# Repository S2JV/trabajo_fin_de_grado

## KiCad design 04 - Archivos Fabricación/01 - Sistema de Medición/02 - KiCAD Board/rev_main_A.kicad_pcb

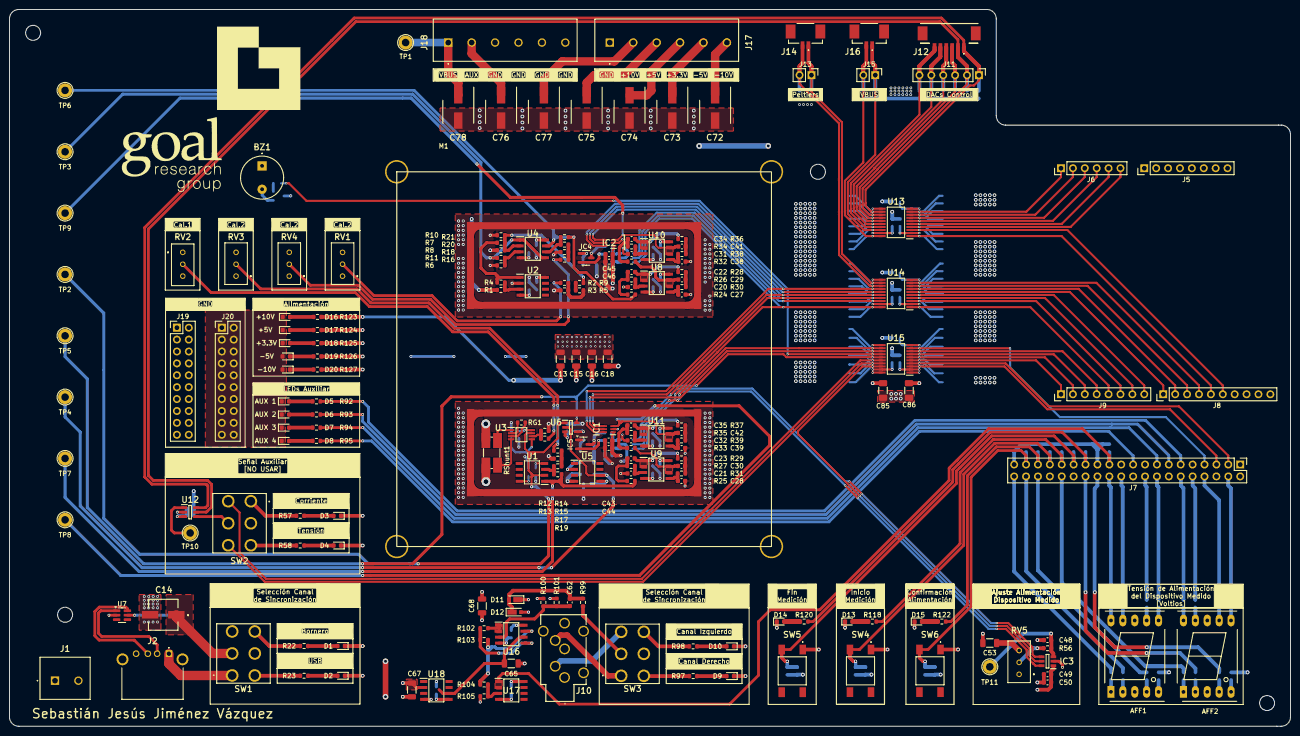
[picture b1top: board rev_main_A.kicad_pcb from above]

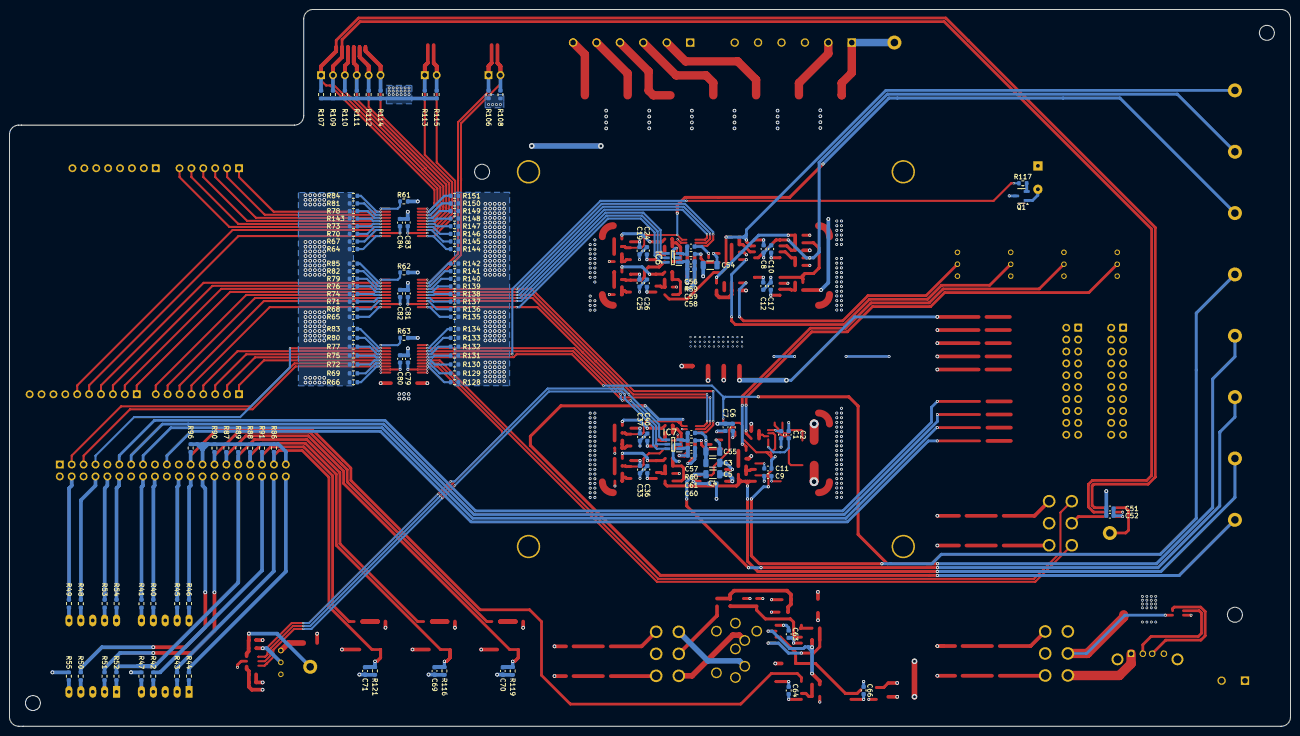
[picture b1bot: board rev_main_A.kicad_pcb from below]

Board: 4 copper layers, 273.5 x 153.0 mm, 334 parts (134 on the bottom side), 197 nets.

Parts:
AFF1, AFF2: TDSR1050; 7SegmentLED_LTS6760_LTS6780
BZ1: CMI-0955-05TH
C1, C2, C6, C7, C8, C9, C10, C11, C12, C17, C19, C24, C25, C26, C33, C36, C37, C40, C43, C45, C49, C51, C56, C57, C58, C60, C63, C64, C79, C80, C81, C82, C83, C84: 0.1u; C_0603_1608Metric
C3, C13, C15, C16, C18, C53, C54, C55, C65, C67, C68: 10u; C_1206_3216Metric
C4, C44, C46, C50, C52, C59, C61, C62, C66, C69, C70, C71: 1u; C_0603_1608Metric
C5: 47u; C_1206_3216Metric
C14: 100u; 865080343009
C20, C21: 100p; C_0603_1608Metric
C22, C23, C29, C30, C34, C35, C41, C42: 1n; C_0603_1608Metric
C27, C28: 430p; C_0603_1608Metric
C31, C32: 680p; C_0603_1608Metric
C38, C39: 910p; C_0603_1608Metric
C48: 15n; C_0603_1608Metric
C72, C73, C74, C75, C76, C77, C78: 47u; CAPAE660X770N
C85, C86: 10u; C_1206_3216Metric_Pad1.33x1.80mm_HandSolder
D1, D2, D3, D4, D5, D6, D7, D8, D9, D10, D13, D15: LED (G); LED_0603_1608Metric
D11, D12: 1V; D_MicroSMP_AK
D14, D16, D17, D18, D19, D20: LED (R); LED_0603_1608Metric
H1, H2, H3, H4: MountingHole; MountingHole_3.2mm_M3
IC1, IC2: AD7476AAKSZ-REEL7; AD7476AAKSZ
IC3, IC6, IC7: ADC121S021CIMFX/NOPB; ADC121S021CIMFXNOPB
IC4, IC5: TMP235A2DBZR; SOT-23-3
J1: Screw_Terminal_01x02; Screw Terminal 2P
J2: USB-1125-GF-B; USB1125GFB [USBA]
J3, J4: MS488-10C
J5: Arduino Power Shield; PinHeader_1x08_P2.54mm_Vertical
J6: Arduino Analog Shield; PinHeader_1x06_P2.54mm_Vertical
J7: Raspberry Pi Shield; PinHeader_2x20_P2.54mm_Vertical
J8: Arduino Digital Shield II; PinHeader_1x10_P2.54mm_Vertical
J9: Arduino Digital Shield I; PinHeader_1x08_P2.54mm_Vertical
J10: SJ1-3533NS; Conector Jack - SJ1-3533NS
J11: Pines; PinHeader_1x06_P2.54mm_Vertical
J12: PicoBlade 6P
J13, J15: PinHeader_1x02_P2.54mm_Vertical
J14, J16: PicoBlade 2P
J17, J18: Screw_Terminal_01x06; Screw Terminal 6P
J19, J20: Conn_02x07_Top_Bottom; PinHeader_2x10_P2.54mm_Vertical
M1: Fan; MC002110
Q1: MMBT4401; SOT-23-3
R1, R4, R6, R7, R8, R11, R19, R40, R41, R42, R43, R44, R45, R46, R47, R48, R49, R50, R51, R52, R53, R54, R55, R116, R117, R119, R121: 1k; R_0603_1608Metric
R2, R13, R14, R16: 200k; R_0603_1608Metric
R3, R12, R15, R18, R59, R60: 100; R_0603_1608Metric
R5, R20: 900; R_0603_1608Metric
R9, R99: 0; R_0603_1608Metric
R10, R103, R105: 100k; R_0603_1608Metric
R17: 1k4; R_0603_1608Metric
R21: 24k; R_0603_1608Metric
R22, R23, R57, R58, R92, R93, R94, R95, R97, R98, R118, R120, R122, R125: 130; R_0603_1608Metric
R24, R25: 1.1k; R_0603_1608Metric
R26, R27: 4.87k; R_0603_1608Metric
R28, R29: 845; R_0603_1608Metric
R30, R31: 1.82k; R_0603_1608Metric
R32, R33: 698; R_0603_1608Metric
R34, R35: 1.58k; R_0603_1608Metric
R36, R37: 715; R_0603_1608Metric
R38, R39: 1.21k; R_0603_1608Metric
R56, R61, R62, R63, R64, R65, R66, R67, R68, R69, R70, R71, R72, R73, R74, R75, R76, R77, R78, R79, R80, R81, R82, R83, R84, R85, R86, R87, R88, R89, R90, R91, R96, R102, R128, R129, R130, R131, R132, R133, R134, R135, R136, R137, R138, R139, R140, R141, R142, R143, R144, R145, R146, R147, R148, R149, R150, R151: 10k; R_0603_1608Metric
R100, R101: 32k; R_0603_1608Metric
R104: 51.5k; R_0603_1608Metric
R106, R107, R108, R109, R110, R111, R112, R113, R114, R115: R; R_0603_1608Metric
R123, R126: 800; R_0603_1608Metric
R124, R127: 300; R_0603_1608Metric
RG1: 60.6; R_0603_1608Metric
RShunt1: 10m; R_Shunt_Ohmite_LVK24
RV1, RV2, RV3, RV4, RV5: 50k; PV36W201C01B00
SW1, SW2, SW3: 100DP1T1B1M2QEH; SW Palanca 100DP1T1B1M2QEH
SW4, SW5, SW6: SW_Push; SW Tactile
TP1, TP2, TP3, TP4, TP5, TP6, TP7, TP8, TP9, TP10, TP11: TestPoint; TestPoint_Loop_D2.60mm_Drill1.6mm_Beaded
U1, U2, U4, U16, U17: OPA210IDBVR; OPA2107AU2K5
U3: INA849DGKT
U5: REF5030AIDR
U6: TLV3601QDBVRQ1
U7: IP4234CZ6,125; SC-74-6_1.55x2.9mm_P0.95mm
U8, U9, U10, U11: AD8656ARZ
U12: DAC121S101CIMK_NOPB
U13, U14, U15: TXS0108EPWRG4
U18: REF5025AIDR; REF5030AIDR

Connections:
+3.3V: C74.1, C80.1, C82.1, C84.1, C86.1, J5.5, J5.7, J7.1, J7.17, J17.4, R47.1, R61.1, R62.1, R63.1, R125.2, SW1.5 (B), SW2.2 (B), SW3.5 (B), SW4.1, SW5.1, SW6.1, U13.2 (VCCA), U14.2 (VCCA), U15.2 (VCCA)
+5V: BZ1.1 (+), C3.1, C6.1, C16.1, C19.1, C25.1, C33.1, C37.1, C43.2, C44.2, C45.2, C46.2, C49.2, C50.2, C51.2, C52.2, C53.1, C54.1, C55.1, C58.2, C59.2, C60.2, C61.2, C63.1, C64.1, C67.1, C68.1, C75.1, C79.1, C81.1, C83.1, C85.1, IC1.1 (VDD), IC2.1 (VDD), IC3.1 (VDD), IC4.1 (VDD), IC5.1 (VDD), IC6.1 (VDD), IC7.1 (VDD), J5.4, J7.2, J17.3, R100.1, R124.2, RV1.1, RV2.3, RV3.1, RV4.1, RV5.3, U5.2 (Vin), U6.3 (V+), U8.8 (V+), U9.8 (V+), U10.8 (V+), U11.8 (V+), U12.3 (VA), U13.19 (VCCB), U14.19 (VCCB), U15.19 (VCCB), U16.8 (V+), U17.8 (V+), U18.2 (Vin)
+10V: C1.2, C8.1, C9.1, C12.1, C13.1, C77.1, J17.2, R123.2, U1.8 (V+), U2.8 (V+), U3.8 (Vs+), U4.8 (V+)
-5V: C7.1, C18.1, C24.1, C26.1, C36.1, C40.1, C73.1, J17.5, R127.2, RV1.3, RV2.1, RV3.3, RV4.3, U6.4 (V-), U8.4 (V-), U9.4 (V-), U10.4 (V-), U11.4 (V-)
-10V: C2.2, C10.1, C11.1, C15.1, C17.1, C72.1, J17.6, R126.2, U1.4 (V-), U2.4 (V-), U3.5 (Vs-), U4.4 (V-)
/006_Conn_FPGA1/BUZZER_{FPGA}: J9.3, R77.1, U15.7 (A6)
/006_Conn_FPGA1/CD_{BUS,ADC,FPGA}: J9.5, R65.1, U14.1 (A1)
/006_Conn_FPGA1/CLK_{4MHz,FPGA}: J9.7, R71.1, U14.4 (A3)
/006_Conn_FPGA1/CLK_{ADC,FPGA}: J9.8, R74.1, U14.5 (A4)
/006_Conn_FPGA1/CLK_{DAC,FPGA}: J6.2, R81.1, U13.8 (A7)
/006_Conn_FPGA1/CS_{ADC,FPGA}: J8.2, R79.1, U14.7 (A6)
/006_Conn_FPGA1/DATA_{BUS,ADC,FPGA}: J7.5, R66.1, U15.3 (A2)
/006_Conn_FPGA1/DATA_{I,ADC,FPGA}: J9.4, R80.1, U15.8 (A7)
/006_Conn_FPGA1/DATA_{TEMP,I,FPGA}: J7.7, R83.1, U15.9 (A8)
/006_Conn_FPGA1/DATA_{TEMP,V,FPGA}: J9.6, R68.1, U14.3 (A2)
/006_Conn_FPGA1/DATA_{V,ADC,FPGA}: J8.1, R76.1, U14.6 (A5)
/006_Conn_FPGA1/DIN_{DAC,AUX,FPGA}: J6.6, R70.1, U13.4 (A3)
/006_Conn_FPGA1/DIN_{DAC,BUS,FPGA}: J6.5, R73.1, U13.5 (A4)
/006_Conn_FPGA1/DIN_{DAC,PEL,I,FPGA}: J6.3, R78.1, U13.7 (A6)
/006_Conn_FPGA1/DIN_{DAC,PEL,V,FPGA}: J6.4, R143.1, U13.6 (A5)
/006_Conn_FPGA1/DIN_{I,AUX,FPGA}: J7.3, R69.1, U15.4 (A3)
/006_Conn_FPGA1/DIN_{V,AUX,FPGA}: J9.1, R72.1, U15.5 (A4)
/006_Conn_FPGA1/ENABLE_{BUS,AUX,FPGA}: J8.6, R67.1, U13.3 (A2)
/006_Conn_FPGA1/ENABLE_{BUS,FPGA}: J8.5, R64.1, U13.1 (A1)
/006_Conn_FPGA1/ENABLE_{PEL,I,FPGA}: J8.4, R85.1, U14.9 (A8)
/006_Conn_FPGA1/ENABLE_{PEL,V,FPGA}: J8.3, R82.1, U14.8 (A7)
/006_Conn_FPGA1/LED_{AUX,1}: J7.11, R92.2
/006_Conn_FPGA1/LED_{AUX,2}: J7.13, R93.2
/006_Conn_FPGA1/LED_{AUX,3}: J7.15, R94.2
/006_Conn_FPGA1/LED_{AUX,4}: J7.19, R95.2
/006_Conn_FPGA1/Protection_{Trigger,FPGA}: J9.2, R75.1, U15.6 (A5)
/006_Conn_FPGA1/SYNC_{DAC,FPGA}: J6.1, R84.1, U13.9 (A8)
ADC_{I,In}: C42.2, IC1.3 (VIN), TP8.1, U11.6 (-), U11.7
ADC_{V,In}: C41.2, IC2.3 (VIN), TP9.1, U10.6 (-), U10.7
BUZZER: R117.2, R132.1, U15.14 (B6)
CLK_{4MHz}: IC3.4 (SCLK), IC6.4 (SCLK), IC7.4 (SCLK), R137.1, U14.17 (B3)
CLK_{ADC}: IC1.4 (SCLK), IC2.4 (SCLK), R138.1, U14.16 (B4)
CLK_{DAC}: J11.2, J12.2, R109.1, R150.1, U12.5 (SCLK), U13.13 (B7)
CS_{ADC}: IC1.6 (~CS), IC2.6 (~CS), R140.1, U14.14 (B6)
CS_{BUS,ADC}: IC3.6 (~CS), IC6.6 (~CS), IC7.6 (~CS), R135.1, U14.20 (B1)
DATA_{BUS,ADC}: IC3.5 (SDATA), R128.1, U15.18 (B2)
DATA_{I,ADC}: IC1.5 (SDATA), R133.1, U15.13 (B7)
DATA_{TEMP,I}: IC7.5 (SDATA), R134.1, U15.12 (B8)
DATA_{TEMP,V}: IC6.5 (SDATA), R136.1, U14.18 (B2)
DATA_{V,ADC}: IC2.5 (SDATA), R139.1, U14.15 (B5)
DIN_{DAC,AUX}: J11.6, J12.6, R114.1, R146.1, U13.17 (B3)
DIN_{DAC,BUS}: J11.5, J12.5, R112.1, R147.1, U13.16 (B4)
DIN_{DAC,PEL,I}: J11.3, J12.3, R110.1, R149.1, U13.14 (B6)
DIN_{DAC,PEL,V}: J11.4, J12.4, R111.1, R148.1, U13.15 (B5)
DIN_{I,AUX}: R129.1, SW2.6 (C), U15.17 (B3)
DIN_{V,AUX}: R130.1, SW2.4 (A), U15.16 (B4)
Display1_{a}: J7.18, R40.1
Display1_{b}: J7.16, R41.1
Display1_{c}: J7.36, R42.1
Display1_{d}: J7.38, R43.1
Display1_{e}: J7.40, R44.1
Display1_{f}: J7.22, R45.1
Display1_{g}: J7.24, R46.1
Display2_{a}: J7.8, R48.1
Display2_{b}: J7.4, R49.1
Display2_{c}: J7.26, R50.1
Display2_{d}: J7.28, R51.1
Display2_{e}: J7.32, R52.1
Display2_{f}: J7.10, R53.1
Display2_{g}: J7.12, R54.1
ENABLE_{BUS,AUX}: J15.1, J16.1, R113.1, R145.1, U13.18 (B2)
ENABLE_{BUS}: J15.2, J16.2, R115.1, R144.1, U13.20 (B1)
ENABLE_{PEL,I}: J13.1, J14.1, R106.1, R142.1, U14.12 (B8)
ENABLE_{PEL,V}: J13.2, J14.2, R108.1, R141.1, U14.13 (B7)
GND: AFF1.3 (C.A.), AFF1.8 (C.A.), AFF2.3 (C.A.), AFF2.8 (C.A.), C1.1, C2.1, C3.2, C4.2, C5.2, C6.2, C7.2, C8.2, C9.2, C10.2, C11.2, C12.2, C13.2, C14.2, C15.2, C16.2, C17.2, C18.2, C19.2, C20.2, C21.2, C24.2, C25.2, C26.2, C27.2, C28.2, C31.2, C32.2, C33.2, C36.2, C37.2, C38.2, C39.2, C40.2, C43.1, C44.1, C45.1, C46.1, C48.2, C49.1, C50.1, C51.1, C52.1, C53.2, C54.2, C55.2, C56.2, C57.2, C58.1, C59.1, C60.1, C61.1, C63.2, C64.2, C65.2, C66.2, C67.2, C68.2, C69.2, C70.2, C71.2, C72.2, C73.2, C74.2, C75.2, C76.2, C77.2, C78.2, C79.2, C80.2, C81.2, C82.2, C83.2, C84.2, C85.2, C86.2, D1.1 (K), D2.1 (K), D3.1 (K), D4.1 (K), D5.1 (K), D6.1 (K), D7.1 (K), D8.1 (K), D9.1 (K), D10.1 (K), D11.1 (K), D12.2 (A), D13.1 (K), D14.1 (K), D15.1 (K), D16.1 (K), D17.1 (K), D18.1 (K), D19.2 (A), D20.2 (A), IC1.2 (GND), IC2.2 (GND), IC3.2 (GND), IC4.3 (GND), IC5.3 (GND), IC6.2 (GND), IC7.2 (GND), J1.1, J2.4 (GND), J2.5 (Shield), J3.1 (Shield), J4.1 (Shield), J5.2, J5.3, J7.6, J7.9, J7.14, J7.20, J7.25, J7.30, J7.34, J7.39, J8.7, J10.1, J17.1, J18.3, J18.4, J18.5, J18.6, J19.1, J19.2, J19.3, J19.4, J19.5, J19.6, J19.7, J19.8, J19.9, J19.10, J19.11, J19.12, J19.13, J19.14, J19.15, J19.16, J19.17, J19.18, J19.19, J19.20, J20.1, J20.2, J20.3, J20.4, J20.5, J20.6, J20.7, J20.8, J20.9, J20.10, J20.11, J20.12, J20.13, J20.14, J20.15, J20.16, J20.17, J20.18, J20.19, J20.20, M1.1 (+), Q1.3 (E), R3.1, R6.1, R10.1, R12.1, R15.2, R18.2, R55.1, R64.2, R65.2, R66.2, R67.2, R68.2, R69.2, R70.2, R71.2, R72.2, R73.2, R74.2, R75.2, R76.2, R77.2, R78.2, R79.2, R80.2, R81.2, R82.2, R83.2, R84.2, R85.2, R86.2, R87.2, R88.2, R89.2, R90.2, R91.2, R96.2, R101.2, R105.2, R106.2, R107.2, R108.2, R109.2, R110.2, R111.2, R112.2, R113.2, R114.2, R115.2, R116.2, R119.2, R121.2, R128.2, R129.2, R130.2, R131.2, R132.2, R133.2, R134.2, R135.2, R136.2, R137.2, R138.2, R139.2, R140.2, R141.2, R142.2, R143.2, R144.2, R145.2, R146.2, R147.2, R148.2, R149.2, R150.2, R151.2, RV5.1, U2.2 (-), U5.4 (GND), U7.2 (VN), U12.2 (GND), U13.11 (GND), U14.11 (GND), U15.11 (GND), U16.4 (V-), U17.4 (V-), U18.4 (GND)
I_{Measure}: R19.2, R25.1, TP7.1, U1.1
unnamed: AFF1.5 (DP), R47.2
unnamed: AFF1.7 (a), R40.2
unnamed: AFF1.6 (b), R41.2
unnamed: AFF1.4 (c), R42.2
unnamed: AFF1.2 (d), R43.2
unnamed: AFF1.1 (e), R44.2
unnamed: AFF1.9 (f), R45.2
unnamed: AFF1.10 (g), R46.2
unnamed: AFF2.5 (DP), R55.2
unnamed: AFF2.7 (a), R48.2
unnamed: AFF2.6 (b), R49.2
unnamed: AFF2.4 (c), R50.2
unnamed: AFF2.2 (d), R51.2
unnamed: AFF2.1 (e), R52.2
unnamed: AFF2.9 (f), R53.2
unnamed: AFF2.10 (g), R54.2
unnamed: BZ1.2 (-), Q1.1 (C)
unnamed: C22.1, R24.2, R26.1
unnamed: C23.1, R25.2, R27.1
unnamed: C29.1, R28.2, R30.1
unnamed: C30.1, R29.2, R31.1
unnamed: C34.1, R32.2, R34.1
unnamed: C35.1, R33.2, R35.1
unnamed: C41.1, R36.2, R38.1
unnamed: C42.1, R37.2, R39.1
unnamed: D1.2 (A), R22.1
unnamed: D2.2 (A), R23.1
unnamed: D3.2 (A), R57.1
unnamed: D4.2 (A), R58.1
unnamed: D5.2 (A), R92.1
unnamed: D6.2 (A), R93.1
unnamed: D7.2 (A), R94.1
unnamed: D8.2 (A), R95.1
unnamed: D9.2 (A), R97.1
unnamed: D10.2 (A), R98.1
unnamed: C62.1, D11.2 (A), D12.1 (K), R99.2
unnamed: D13.2 (A), R118.1
unnamed: D14.2 (A), R120.1
unnamed: D15.2 (A), R122.1
unnamed: D16.2 (A), R123.1
unnamed: D17.2 (A), R124.1
unnamed: D18.2 (A), R125.1
unnamed: D19.1 (K), R126.1
unnamed: D20.1 (K), R127.1
unnamed: C48.1, IC3.3 (VIN), R56.2, TP11.1
unnamed: IC4.2 (VOUT), R59.1
unnamed: IC5.2 (VOUT), R60.1
unnamed: C56.1, IC6.3 (VIN), R59.2
unnamed: C57.1, IC7.3 (VIN), R60.2
unnamed: J1.2, SW1.3 (C)
unnamed: J2.3 (D+), U7.6
unnamed: J2.2 (D-), U7.1
unnamed: J2.1 (VBUS), SW1.1 (A)
unnamed: J10.2, SW3.3 (C)
unnamed: J10.3, SW3.1 (A)
unnamed: Q1.2 (B), R117.1
unnamed: R2.1, RV1.2
unnamed: R2.2, R3.2, R5.1
unnamed: R4.2, R7.1, U2.1
unnamed: R5.2, R9.1
unnamed: R13.2, RV2.2
unnamed: R14.1, RV3.2
unnamed: R14.2, R15.1, R17.1
unnamed: R16.1, RV4.2
unnamed: R16.2, R18.1, R20.2
unnamed: R22.2, SW1.6 (C)
unnamed: R23.2, SW1.4 (A)
unnamed: R56.1, RV5.2
unnamed: R57.2, SW2.1 (A)
unnamed: R58.2, SW2.3 (C)
unnamed: R97.2, SW3.4 (A)
unnamed: R98.2, SW3.6 (C)
unnamed: R99.1, SW3.2 (B)
unnamed: R103.2, R104.1, U16.7
unnamed: RG1.1, U3.2 (Rg)
unnamed: RG1.2, U3.3 (Rg)
unnamed: R17.2, R19.1, U1.3 (+)
unnamed: TP2.1, U1.2 (-), U3.7, U6.1 (+)
unnamed: R1.2, R4.1, U2.3 (+)
unnamed: RShunt1.3, U3.4 (+)
unnamed: RShunt1.2, U3.1 (-)
unnamed: R12.2, R13.1, U3.6 (Ref)
unnamed: R6.2, R11.1, U4.3 (+)
unnamed: R7.2, R8.2, R9.2, R10.2, U4.2 (-)
unnamed: R11.2, TP3.1, U4.1, U4.5 (+)
unnamed: R20.1, R21.1, U4.6 (-)
unnamed: C4.1, U5.5 (Trim/NR)
unnamed: C5.1, TP4.1, U5.6 (Vout), U6.2 (-)
unnamed: C20.1, R26.2, U8.3 (+)
unnamed: C22.2, R28.1, U8.1, U8.2 (-)
unnamed: C27.1, R30.2, U8.5 (+)
unnamed: C29.2, R32.1, U8.6 (-), U8.7
unnamed: C21.1, R27.2, U9.3 (+)
unnamed: C23.2, R29.1, U9.1, U9.2 (-)
unnamed: C28.1, R31.2, U9.5 (+)
unnamed: C30.2, R33.1, U9.6 (-), U9.7
unnamed: C31.1, R34.2, U10.3 (+)
unnamed: C34.2, R36.1, U10.1, U10.2 (-)
unnamed: C38.1, R38.2, U10.5 (+)
unnamed: C32.1, R35.2, U11.3 (+)
unnamed: C35.2, R37.1, U11.1, U11.2 (-)
unnamed: C39.1, R39.2, U11.5 (+)
unnamed: SW2.5 (B), U12.4 (DIN)
unnamed: TP10.1, U12.1 (VOUT)
unnamed: R61.2, U13.10 (OE)
unnamed: R62.2, U14.10 (OE)
unnamed: R63.2, U15.10 (OE)
unnamed: C62.2, R100.2, R101.1, U16.3 (+)
unnamed: R102.1, U16.1, U16.2 (-)
unnamed: R102.2, R103.1, U16.5 (+)
unnamed: C65.1, U16.6 (-), U18.6 (Vout)
unnamed: R104.2, R105.1, U17.3 (+)
unnamed: C66.1, U18.5 (Trim/NR)
Protection_{Trigger}: R131.1, TP5.1, U6.5, U15.15 (B5)
READY_{VBUS,LED}: J7.35, R91.1, R122.2
READY_{VBUS}: C71.1, J7.37, R86.1, R121.1, SW6.2
START_{LED}: J7.31, R89.1, R118.2
START_{MEASURE}: C69.1, J7.33, R88.1, R116.1, SW4.2
STOP_{LED}: J7.27, R90.1, R120.2
STOP_{MEASURE}: C70.1, J7.29, R87.1, R119.1, SW5.2
SYNC_{DAC}: J11.1, J12.1, R107.1, R151.1, U12.6 (SYNC), U13.12 (B8)
SYNC_{MEASURE}: J7.23, R96.1, U17.1, U17.2 (-)
VBUS: C78.1, J18.1, R8.1, RShunt1.1, TP1.1
VBUS_{USB}: C14.1, RShunt1.4, SW1.2 (B), U7.5 (VP)
V_{BUS,AUX}: C76.1, J18.2, R1.1
V_{Measure}: R21.2, R24.1, TP6.1, U4.7

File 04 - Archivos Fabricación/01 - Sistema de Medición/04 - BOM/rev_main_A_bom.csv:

"DNP","Reference","Value","Manufacturer_Part_Number","Footprint","Qty"
"","U8,U9,U10,U11","AD8676ARZ","AD8656ARZ","ICs - Amplificadores Operacionales:AD8656ARZ","4"
"","U13,U14,U15","TXS0108EPWRG4","TXS0108EPWRG4","ICs - Adaptadores Lógicos:TXS0108EPWRG4","3"
"","U1,U2,U4,U16,U17","OPA2210IDBVR","OPA210IDBVR","ICs - Amplificadores Operacionales:OPA2107AU2K5","5"
"","U18","REF5025AIDR","REF5025AIDR","ICs - Referencias:REF5030AIDR","1"
"","U12","DAC121S101CIMK_NOPB","DAC121S101CIMK_NOPB","ICs - ADCs:DAC121S101CIMK_NOPB","1"
"","U7","IP4234CZ6,125","IP4234CZ6,125","Package_TO_SOT_SMD:SC-74-6_1.55x2.9mm_P0.95mm","1"
"","U6","TLV3601QDBVRQ1","TLV3601QDBVRQ1","ICs - Amplificadores Operacionales:TLV3601QDBVRQ1","1"
"","U5","REF5030AIDR","REF5030AIDR","ICs - Referencias:REF5030AIDR","1"
"","U3","INA849DGKT","INA849DGKT","ICs - Amplificadores Operacionales:INA849DGKT","1"
"","TP1,TP2,TP3,TP4,TP5,TP6,TP7,TP8,TP9,TP10,TP11","TestPoint","5006 ","TestPoint:TestPoint_Loop_D2.60mm_Drill1.6mm_Beaded","11"
"","SW4,SW5,SW6","SW_Push","TS04-66-73-BK-100-SMT","Conexiones y Pines:SW Tactile","3"
"","SW1,SW2,SW3","100DP1T1B1M2QEH","100DP1T1B1M2QEH","Conexiones y Pines:SW Palanca 100DP1T1B1M2QEH","3"
"","RV1,RV2,RV3,RV4,RV5","50k","PV36W503C01B00","ICs - Potenciómetro:PV36W201C01B00","5"
"","RShunt1","10m","LVK24R010CER","Resistor_SMD:R_Shunt_Ohmite_LVK24","1"
"","RG1","60.6","","Resistor_SMD:R_0603_1608Metric","1"
"","R56,R61,R62,R63,R64,R65,R66,R67,R68,R69,R70,R71,R72,R73,R74,R75,R76,R77,R78,R79,R80,R81,R82,R83,R84,R85,R86,R87,R88,R89,R90,R91,R96,R102,R128,R129,R130,R131,R132,R133,R134,R135,R136,R137,R138,R139,R140,R141,R142,R143,R144,R145,R146,R147,R148,R149,R150,R151","10k","","Resistor_SMD:R_0603_1608Metric","58"
"","R5,R8,R9,R99","0","","Resistor_SMD:R_0603_1608Metric","4"
"","R38,R39","1.21k","","Resistor_SMD:R_0603_1608Metric","2"
"","R36,R37","715","","Resistor_SMD:R_0603_1608Metric","2"
"","R34,R35","1.58k","","Resistor_SMD:R_0603_1608Metric","2"
"","R32,R33","698","","Resistor_SMD:R_0603_1608Metric","2"
"","R30,R31","1.82k","","Resistor_SMD:R_0603_1608Metric","2"
"","R3,R12,R15,R18,R59,R60","100","","Resistor_SMD:R_0603_1608Metric","6"
"","R28,R29","845","","Resistor_SMD:R_0603_1608Metric","2"
"","R26,R27","4.87k","","Resistor_SMD:R_0603_1608Metric","2"
"","R24,R25","1.1k","","Resistor_SMD:R_0603_1608Metric","2"
"","R22,R23,R57,R58,R92,R93,R94,R95,R97,R98,R118,R120,R122,R125","130","","Resistor_SMD:R_0603_1608Metric","14"
"","R13,R14,R16","200k","","Resistor_SMD:R_0603_1608Metric","3"
"","R124,R127","300","","Resistor_SMD:R_0603_1608Metric","2"
"","R123,R126","800","","Resistor_SMD:R_0603_1608Metric","2"
"","R106,R107,R108,R109,R110,R111,R112,R113,R114,R115","R","","Resistor_SMD:R_0603_1608Metric","10"
"","R100,R101","32k","","Resistor_SMD:R_0603_1608Metric","2"
"","R10,R105","100k","","Resistor_SMD:R_0603_1608Metric","2"
"","R1,R4,R6,R7,R11,R19,R40,R41,R42,R43,R44,R45,R46,R47,R48,R49,R50,R51,R52,R53,R54,R55,R116,R117,R119,R121","1k","","Resistor_SMD:R_0603_1608Metric","26"
"","R104","51.5k","","Resistor_SMD:R_0603_1608Metric","1"
"","R103","125k","","Resistor_SMD:R_0603_1608Metric","1"
"","R21","24k","","Resistor_SMD:R_0603_1608Metric","1"
"","R20","900","","Resistor_SMD:R_0603_1608Metric","1"
"","R17","1k4","","Resistor_SMD:R_0603_1608Metric","1"
"","R2","2M","","Resistor_SMD:R_0603_1608Metric","1"
"","Q1","MMBT4401","MMBT4401","Package_TO_SOT_SMD:SOT-23-3","1"
"","J3,J4","MS488-10C","MS488-10C","Conexiones y Pines:MS488-10C","2"
"","J19,J20","Conn_02x07_Top_Bottom","","Connector_PinHeader_2.54mm:PinHeader_2x10_P2.54mm_Vertical","2"
"","J17,J18","Screw_Terminal_01x06","","Conexiones y Pines:Screw Terminal 6P","2"
"","J14,J16","PicoBlade 2P","","Conexiones y Pines:PicoBlade 2P","2"
"","J13,J15","~","","Connector_PinHeader_2.54mm:PinHeader_1x02_P2.54mm_Vertical","2"
"","J12","PicoBlade 6P","","Conexiones y Pines:PicoBlade 6P","1"
"","J11","Pines","","Connector_PinHeader_2.54mm:PinHeader_1x06_P2.54mm_Vertical","1"
"","J10","SJ1-3533NS","SJ1-3533NS","Conexiones y Pines:Conector Jack - SJ1-3533NS","1"
"","J9","Arduino Digital Shield I","","Connector_PinHeader_2.54mm:PinHeader_1x08_P2.54mm_Vertical","1"
"","J8","Arduino Digital Shield II","","Connector_PinHeader_2.54mm:PinHeader_1x10_P2.54mm_Vertical","1"
"","J7","Raspberry Pi Shield","","Connector_PinHeader_2.54mm:PinHeader_2x20_P2.54mm_Vertical","1"
"","J6","Arduino Analog Shield","","Connector_PinHeader_2.54mm:PinHeader_1x06_P2.54mm_Vertical","1"
"","J5","Arduino Power Shield","","Connector_PinHeader_2.54mm:PinHeader_1x08_P2.54mm_Vertical","1"
"","J2","USB-1125-GF-B","USB-1125-GF-B","Conexiones y Pines:USB1125GFB [USBA]","1"
"","J1","Screw_Terminal_01x02","","Conexiones y Pines:Screw Terminal 2P","1"
"","IC4,IC5","TMP235A2DBZR","TMP235A2DBZR","Package_TO_SOT_SMD:SOT-23-3","2"
"","IC3,IC6,IC7","ADC121S021CIMFX/NOPB","ADC121S021CIMFX/NOPB","ICs - ADCs:ADC121S021CIMFXNOPB","3"
"","IC1,IC2","AD7476AAKSZ-REEL7","AD7476AAKSZ-REEL7","ICs - ADCs:AD7476AAKSZ","2"
"","D14,D16,D17,D18,D19,D20","LED (R)","150060RS75000","LED_SMD:LED_0603_1608Metric","6"
"","D11,D12","1V","MRSE1PK-M3/I","Diode_SMD:D_MicroSMP_AK","2"
"","D1,D2,D3,D4,D5,D6,D7,D8,D9,D10,D13,D15","LED (G)","150060VS75000","LED_SMD:LED_0603_1608Metric","12"
"","C5,C72,C73,C74,C75,C76,C77,C78","47u","","Capacitor_SMD:C_1206_3216Metric,ICs - Condensadores:CAPAE660X770N","8"
"","C4,C44,C46,C50,C52,C59,C61,C62,C66,C69,C70,C71","1u","","Capacitor_SMD:C_0603_1608Metric","12"
"","C38,C39","910p","","Capacitor_SMD:C_0603_1608Metric","2"
"","C31,C32","680p","","Capacitor_SMD:C_0603_1608Metric","2"
"","C3,C13,C15,C16,C18,C53,C54,C55,C65,C67,C68,C85,C86","10u","","Capacitor_SMD:C_1206_3216Metric,Capacitor_SMD:C_1206_3216Metric_Pad1.33x1.80mm_HandSolder","13"
"","C27,C28","430p","","Capacitor_SMD:C_0603_1608Metric","2"
"","C22,C23,C29,C30,C34,C35,C41,C42","1n","","Capacitor_SMD:C_0603_1608Metric","8"
"","C20,C21","100p","","Capacitor_SMD:C_0603_1608Metric","2"
"","C1,C2,C6,C7,C8,C9,C10,C11,C12,C17,C19,C24,C25,C26,C33,C36,C37,C40,C43,C45,C49,C51,C56,C57,C58,C60,C63,C64,C79,C80,C81,C82,C83,C84","0.1u","","Capacitor_SMD:C_0603_1608Metric","34"
"","C48","15n","","Capacitor_SMD:C_0603_1608Metric","1"
"","C14","100u","","ICs - Condensadores:865080343009","1"
"","BZ1","CMI-0955-05TH","CMI-0955-05TH","ICs - Diodos:CMI-0955-05TH","1"
"","AFF1,AFF2","TDSR1050","TDSR1050","Display_7Segment:7SegmentLED_LTS6760_LTS6780","2"

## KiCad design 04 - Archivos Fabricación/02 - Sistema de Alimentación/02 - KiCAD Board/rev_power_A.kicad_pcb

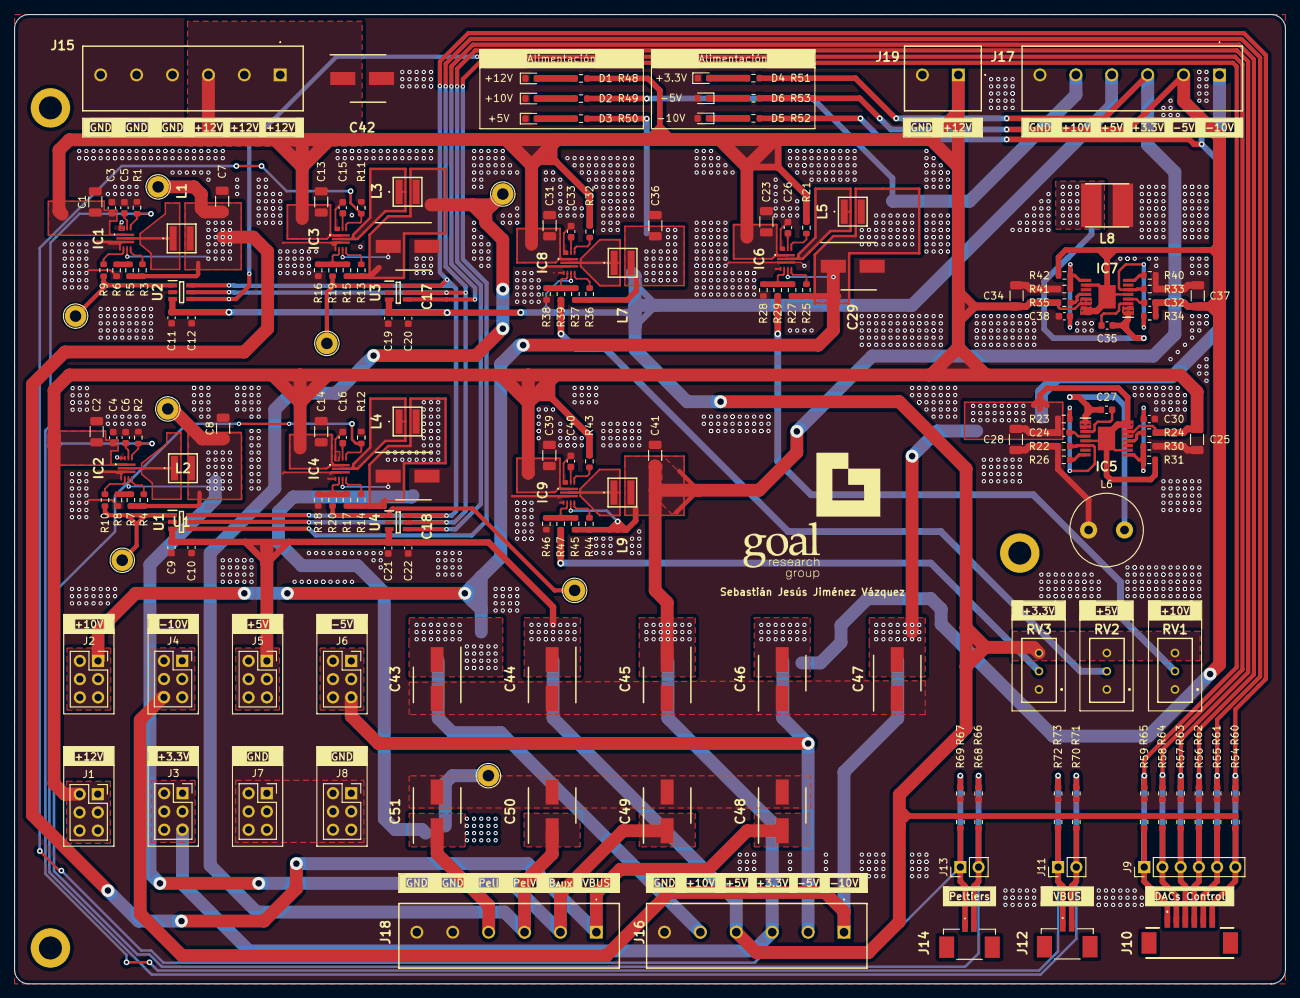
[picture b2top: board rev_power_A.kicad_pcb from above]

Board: 2 copper layers, 177.0 x 135.0 mm, 185 parts (0 on the bottom side), 81 nets.

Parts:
C1, C2, C13, C14, C23, C25, C31, C34, C39: 10u; C_1206_3216Metric
C3, C4, C9, C11, C19, C21: 0.1u; C_0603_1608Metric
C5, C6, C15, C16, C26, C33, C40: 2.2n; C_0603_1608Metric
C7, C8, C36, C41: 47u; C_1206_3216Metric
C10, C12, C20, C22: 1u; C_0603_1608Metric
C17, C18, C29, C42, C43, C44, C45, C46, C47, C48, C49, C50, C51: 47u; CAPAE660X770N
C24, C32: 2.2u; C_0603_1608Metric
C27, C35: 470n; C_0603_1608Metric
C28, C37: 4.7u; C_1206_3216Metric
C30: 180p; C_0603_1608Metric
C38: 56p; C_0603_1608Metric
D1, D2, D3, D4, D5, D6: LED (R); LED_0603_1608Metric
H1, H2, H3: MountingHole; MountingHole_3.2mm_M3_ISO14580_Pad
IC1, IC2: TPS621361; TPS621361RGXT
IC3, IC4, IC6, IC8, IC9: TPS62136RGXR; TPS621361RGXT
IC5, IC7: LM43601PWPR; SOP65P640X120-17N
J1, J2, J3, J4, J5, J6, J7, J8: Conn_02x03_Counter_Clockwise; PinSocket_2x03_P2.54mm_Vertical
J9: PicoBlade 6P; PinHeader_1x06_P2.54mm_Vertical
J10: PicoBlade 6P
J11, J13: PicoBlade 2P; PinHeader_1x02_P2.54mm_Vertical
J12, J14: PicoBlade 2P
J15, J16, J17, J18: Screw_Terminal_01x06; Screw Terminal 6P
J19: Screw Terminal 2P
L1, L2, L3, L4, L5, L7, L9: 1.5u; XAL4020152MEC
L6: 47u; L_Radial_D10.0mm_P5.00mm_Neosid_SD12_style3
L8: 33u; INDM6060X450N
R1, R2, R11, R12, R21, R24, R32, R35, R43: 10k; R_0603_1608Metric
R3, R4, R13, R14, R25, R26, R36, R40, R44: 100k; R_0603_1608Metric
R5, R7: 619k; R_0603_1608Metric
R6, R8: 95.3k; R_0603_1608Metric
R9, R10: 768k; R_0603_1608Metric
R15, R17: 953k; R_0603_1608Metric
R16, R18, R31: 113k; R_0603_1608Metric
R19, R20: 732k; R_0603_1608Metric
R22, R23, R33, R34: 0; R_0603_1608Metric
R27: 1.47M; R_0603_1608Metric
R28, R38: 102k; R_0603_1608Metric
R29, R39, R47: 2M; R_0603_1608Metric
R30, R41: 1M; R_0603_1608Metric
R37: 750k; R_0603_1608Metric
R42: 255k; R_0603_1608Metric
R45: 511k; R_0603_1608Metric
R46: 105k; R_0603_1608Metric
R48, R49, R50, R51, R52, R53: 130; R_0603_1608Metric
R54, R55, R56, R57, R58, R59, R60, R61, R62, R63, R64, R65, R66, R67, R68, R69, R70, R71, R72, R73: R; R_0603_1608Metric
RV1, RV2, RV3: 50k; PV36W201C01B00
TP1, TP2, TP3, TP4, TP5, TP6, TP7, TP8: TestPoint; TestPoint_Loop_D2.60mm_Drill1.6mm_Beaded
U1, U2, U3, U4: DAC121S101CIMK/NOPB; SOT-23-THIN-6

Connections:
+3.3V: C41.1, C45.1, IC9.6 (VOS), J3.1, J3.2, J3.3, J3.4, J3.5, J3.6, J16.3, J17.3, L9.2, R44.2, R45.1, R51.2
+5V: C9.2, C10.2, C11.2, C12.2, C19.2, C20.2, C21.2, C22.2, C36.1, C44.1, IC8.6 (VOS), J5.1, J5.2, J5.3, J5.4, J5.5, J5.6, J16.4, J17.4, L7.2, R36.2, R37.1, R50.2, R54.1, R55.1, R56.1, R57.1, R58.1, R59.1, R68.1, R69.1, R70.1, R72.1, RV1.3, RV2.3, RV3.3, U1.3 (VA), U2.3 (VA), U3.3 (VA), U4.3 (VA)
+10V: C29.1, C43.1, IC6.6 (VOS), J2.1, J2.2, J2.3, J2.4, J2.5, J2.6, J16.5, J17.5, L5.2, R25.2, R27.1, R49.2
+12V: C1.1, C2.1, C3.1, C4.1, C13.1, C14.1, C23.1, C25.1, C31.1, C34.1, C39.1, C42.1, IC1.1 (VIN), IC2.1 (VIN), IC3.1 (VIN), IC4.1 (VIN), IC5.13 (VIN_1), IC5.14 (VIN_2), IC6.1 (VIN), IC7.13 (VIN_1), IC7.14 (VIN_2), IC8.1 (VIN), IC9.1 (VIN), J1.1, J1.2, J1.3, J1.4, J1.5, J1.6, J15.1, J15.2, J15.3, J19.1, R21.1, R24.2, R32.1, R35.2, R43.1, R48.2
-5V: C32.1, C37.2, C46.2, IC7.5 (BIAS), IC7.10 (AGND), IC7.15 (PGND_1), IC7.16 (PGND_2), IC7.17 (EP), J6.1, J6.2, J6.3, J6.4, J6.5, J6.6, J16.2, J17.2, R34.2, R42.1, R53.2
-10V: C24.1, C28.2, C47.2, IC5.5 (BIAS), IC5.10 (AGND), IC5.15 (PGND_1), IC5.16 (PGND_2), IC5.17 (EP), J4.1, J4.2, J4.3, J4.4, J4.5, J4.6, J16.1, J17.1, R23.2, R31.1, R52.2
CLK_{DAC}: J9.5, J10.5, R55.2, R61.1, U1.5 (SCLK), U2.5 (SCLK), U3.5 (SCLK), U4.5 (SCLK)
DIN_{DAC,AUX}: J9.1, J10.1, R59.2, R65.1, U1.4 (DIN)
DIN_{DAC,BUS}: J9.2, J10.2, R58.2, R64.1, U2.4 (DIN)
DIN_{DAC,PEL,I}: J9.3, J10.3, R57.2, R63.1, U4.4 (DIN)
DIN_{DAC,PEL,V}: J9.4, J10.4, R56.2, R62.1, U3.4 (DIN)
ENABLE_{BUS,AUX}: IC2.8 (EN), J11.2, J12.2, R2.1, R70.2, R71.1
ENABLE_{BUS}: IC1.8 (EN), J11.1, J12.1, R1.1, R72.2, R73.1
ENABLE_{PEL,I}: IC4.8 (EN), J13.2, J14.2, R12.1, R66.1, R68.2
ENABLE_{PEL,V}: IC3.8 (EN), J13.1, J14.1, R11.1, R67.1, R69.2
GND: C1.2, C2.2, C3.2, C4.2, C5.1, C6.1, C7.2, C8.2, C9.1, C10.1, C11.1, C12.1, C13.2, C14.2, C15.1, C16.1, C17.2, C18.2, C19.1, C20.1, C21.1, C22.1, C23.2, C25.2, C26.1, C28.1, C29.2, C30.2, C31.2, C33.1, C34.2, C36.2, C37.1, C38.2, C39.2, C40.1, C41.2, C42.2, C43.2, C44.2, C45.2, C46.1, C47.1, C48.2, C49.2, C50.2, C51.2, D1.1 (K), D2.1 (K), D3.1 (K), D4.1 (K), D5.2 (A), D6.2 (A), IC1.3 (GND), IC1.4 (FB2), IC1.10 (MODE), IC1.11 (VSEL), IC2.3 (GND), IC2.4 (FB2), IC2.10 (MODE), IC2.11 (VSEL), IC3.3 (GND), IC3.4 (FB2), IC3.10 (MODE), IC3.11 (VSEL), IC4.3 (GND), IC4.4 (FB2), IC4.10 (MODE), IC4.11 (VSEL), IC6.3 (GND), IC6.4 (FB2), IC6.10 (MODE), IC6.11 (VSEL), IC8.3 (GND), IC8.4 (FB2), IC8.10 (MODE), IC8.11 (VSEL), IC9.3 (GND), IC9.4 (FB2), IC9.10 (MODE), IC9.11 (VSEL), J7.1, J7.2, J7.3, J7.4, J7.5, J7.6, J8.1, J8.2, J8.3, J8.4, J8.5, J8.6, J15.4, J15.5, J15.6, J16.6, J17.6, J18.5, J18.6, J19.2, L6.2, L8.2, R1.2, R2.2, R6.2, R8.2, R11.2, R12.2, R16.2, R18.2, R22.2, R26.1, R28.2, R30.2, R33.2, R38.2, R40.1, R41.2, R46.2, R60.2, R61.2, R62.2, R63.2, R64.2, R65.2, R66.2, R67.2, R71.2, R73.2, RV1.1, RV2.1, RV3.1, U1.2 (GND), U2.2 (GND), U3.2 (GND), U4.2 (GND)
unnamed: D1.2 (A), R48.1
unnamed: D2.2 (A), R49.1
unnamed: D3.2 (A), R50.1
unnamed: D4.2 (A), R51.1
unnamed: D5.1 (K), R52.1
unnamed: D6.1 (K), R53.1
unnamed: IC1.5 (FB), R9.1
unnamed: IC1.7 (PG), R3.2
unnamed: C5.2, IC1.9 (SS/TR)
unnamed: IC1.2 (SW), L1.1
unnamed: IC2.5 (FB), R10.1
unnamed: IC2.7 (PG), R4.2
unnamed: C6.2, IC2.9 (SS/TR)
unnamed: IC2.2 (SW), L2.1
unnamed: IC3.5 (FB), R15.2, R16.1, R19.1
unnamed: IC3.7 (PG), R13.1
unnamed: C15.2, IC3.9 (SS/TR)
unnamed: IC3.2 (SW), L3.1
unnamed: IC4.5 (FB), R17.2, R18.1, R20.1
unnamed: IC4.7 (PG), R14.1
unnamed: C16.2, IC4.9 (SS/TR)
unnamed: IC4.2 (SW), L4.1
unnamed: C27.2, IC5.3 (CBOOT)
unnamed: IC5.12 (EN), R24.1
unnamed: C30.1, IC5.9 (FB), R30.1, R31.2
unnamed: IC5.8 (PGOOD), R26.2
unnamed: C27.1, IC5.1 (SW_1), IC5.2 (SW_2), L6.1
unnamed: IC5.6 (SYNC), R22.1, R23.1
unnamed: C24.2, IC5.4 (VCC)
unnamed: IC6.8 (EN), R21.2
unnamed: IC6.5 (FB), R27.2, R28.1, R29.1
unnamed: IC6.7 (PG), R25.1
unnamed: C26.2, IC6.9 (SS/TR)
unnamed: IC6.2 (SW), L5.1
unnamed: C35.2, IC7.3 (CBOOT)
unnamed: IC7.12 (EN), R35.1
unnamed: C38.1, IC7.9 (FB), R41.1, R42.2
unnamed: IC7.8 (PGOOD), R40.2
unnamed: C35.1, IC7.1 (SW_1), IC7.2 (SW_2), L8.1
unnamed: IC7.6 (SYNC), R33.1, R34.1
unnamed: C32.2, IC7.4 (VCC)
unnamed: IC8.8 (EN), R32.2
unnamed: IC8.5 (FB), R37.2, R38.1, R39.1
unnamed: IC8.7 (PG), R36.1
unnamed: C33.2, IC8.9 (SS/TR)
unnamed: IC8.2 (SW), L7.1
unnamed: IC9.8 (EN), R43.2
unnamed: IC9.5 (FB), R45.2, R46.1, R47.1
unnamed: IC9.7 (PG), R44.1
unnamed: C40.2, IC9.9 (SS/TR)
unnamed: IC9.2 (SW), L9.1
unnamed: R5.2, R6.1
unnamed: R7.2, R8.1
unnamed: R29.2, RV1.2
unnamed: R39.2, RV2.2
unnamed: R47.2, RV3.2
unnamed: R10.2, TP3.1, U1.1 (VOUT)
unnamed: R9.2, TP4.1, U2.1 (VOUT)
unnamed: R19.2, TP7.1, U3.1 (VOUT)
unnamed: R20.2, TP8.1, U4.1 (VOUT)
Peltier_{I}: C18.1, C51.1, IC4.6 (VOS), J18.4, L4.2, R14.2, R17.1, TP6.1
Peltier_{V}: C17.1, C50.1, IC3.6 (VOS), J18.3, L3.2, R13.2, R15.1, TP5.1
SYNC_{DAC}: J9.6, J10.6, R54.2, R60.1, U1.6 (SYNC), U2.6 (SYNC), U3.6 (SYNC), U4.6 (SYNC)
VBUS: C7.1, C48.1, IC1.6 (VOS), J18.1, L1.2, R3.1, R5.1, TP1.1
V_{BUS,AUX}: C8.1, C49.1, IC2.6 (VOS), J18.2, L2.2, R4.1, R7.1, TP2.1

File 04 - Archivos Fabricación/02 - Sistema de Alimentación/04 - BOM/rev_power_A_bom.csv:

"DNP","Reference","Value","Manufacturer_Part_Number","Footprint","Qty"
"","R23,R34","0","MCT0603MZ0000ZP500","Resistor_SMD:R_0603_1608Metric","2"
"","C38","56p","C0603C560J5GACTU","Capacitor_SMD:C_0603_1608Metric","1"
"","C30","180p","CL10C181JB81PND","Capacitor_SMD:C_0603_1608Metric","1"
"","C5,C6,C15,C16,C26,C33,C40","2.2n","C0603C222J5GAC","Capacitor_SMD:C_0603_1608Metric","7"
"","C3,C4,C9,C11,C19,C21","0.1u","MCAST168SB5104KTNA01","Capacitor_SMD:C_0603_1608Metric","6"
"","C27,C35","470n","CL10B472KB8NNND","Capacitor_SMD:C_0603_1608Metric","2"
"","C10,C12,C20,C22","1u","AMK063AC6105MP-F","Capacitor_SMD:C_0603_1608Metric","4"
"","L1,L2,L3,L4,L5,L7,L9","1.5u","XAL4020-152MEC","ICs - Inductores de Potencia:XAL4020152MEC","7"
"","C24,C32","2.2u","TMK107ABJ225KA-T","Capacitor_SMD:C_0603_1608Metric","2"
"","C28,C37","4.7u","T491A475M016AT","Capacitor_SMD:C_1206_3216Metric","2"
"","C1,C2,C13,C14,C23,C25,C31,C34,C39","10u","T491A106K020AT","Capacitor_SMD:C_1206_3216Metric","9"
"","L8","33u","SRN6045-330M","ICs - Inductores de Potencia:INDM6060X450N","1"
"","C7,C8,C17,C18,C36,C41","47u","TMCMA1A476MTRF","-- valores mixtos --","6"
"","C29,C42,C43,C44,C45,C46,C47,C48,C49,C50,C51","47u","865230445005","ICs - Condensadores:CAPAE660X770N","11"
"","L6","47u","7447720470","Inductor_THT:L_Radial_D10.0mm_P5.00mm_Neosid_SD12_style3","1"
"","R48,R49,R50,R51,R52,R53","130","ERA-3AEB131V","Resistor_SMD:R_0603_1608Metric","6"
"","R1,R2,R11,R12,R21,R24,R32,R35,R43","10k","RT0603DRE0710KL","Resistor_SMD:R_0603_1608Metric","9"
"","RV1,RV2,RV3","50k","PV36W503C01B00","ICs - Potenciómetro:PV36W201C01B00","3"
"","R6,R8","95.3k","RT0603FRE0795K3L","Resistor_SMD:R_0603_1608Metric","2"
"","R3,R4,R13,R14,R25,R26,R36,R40,R44","100k","AT0603DRD07100KL","Resistor_SMD:R_0603_1608Metric","9"
"","R28,R38","102k","ERA-3AEB1023V","Resistor_SMD:R_0603_1608Metric","2"
"","R46","105k","RT0603DRD07105KL","Resistor_SMD:R_0603_1608Metric","1"
"","R16,R18,R31","113k","ERA-3AED1133V","Resistor_SMD:R_0603_1608Metric","3"
"","R42","255k","RT0603BRD07255KL","Resistor_SMD:R_0603_1608Metric","1"
"","R45","511k","RT0603DRE07511KL","Resistor_SMD:R_0603_1608Metric","1"
"","R5,R7","619k","RT0603FRE07619KL","Resistor_SMD:R_0603_1608Metric","2"
"","R19,R20","732k","RN73H1JTTD7323B25","Resistor_SMD:R_0603_1608Metric","2"
"","R37","750k","RT0603BRD07750KL","Resistor_SMD:R_0603_1608Metric","1"
"","R9,R10","768k","RN73H1JTTD7683F100","Resistor_SMD:R_0603_1608Metric","2"
"","R15,R17","953k","CPF0603B953KE","Resistor_SMD:R_0603_1608Metric","2"
"","R30,R41","1M","RT0603DRD071ML","Resistor_SMD:R_0603_1608Metric","2"
"","R27","1.47M","MCT0603MD1504BP500","Resistor_SMD:R_0603_1608Metric","1"
"","R29,R39,R47","2M","MCT0603MD2004BP500","Resistor_SMD:R_0603_1608Metric","3"
"DNP","R22,R33,R54,R55,R56,R57,R58,R59,R60,R61,R62,R63,R64,R65,R66,R67,R68,R69,R70,R71,R72,R73","-- valores mixtos --","","Resistor_SMD:R_0603_1608Metric","22"
"","J1,J2,J3,J4,J5,J6,J7,J8","Conn_02x03_Counter_Clockwise","2X03","Connector_PinSocket_2.54mm:PinSocket_2x03_P2.54mm_Vertical","8"
"","U1,U2,U3,U4","DAC121S101CIMK/NOPB","DAC121S101CIMK/NOPB","ICS - DACs:SOT-23-THIN-6","4"
"","D1,D2,D3,D4,D5,D6","LED (R)","150060RS75000","LED_SMD:LED_0603_1608Metric","6"
"","IC5,IC7","LM43601PWPR","LM43601PWPR","ICs - Gestión de Energía:SOP65P640X120-17N","2"
"","J11,J13","PicoBlade 2P","1X02","Connector_PinHeader_2.54mm:PinHeader_1x02_P2.54mm_Vertical","2"
"","J12,J14","PicoBlade 2P","53261-0271","Conexiones y Pines:PicoBlade 2P","2"
"","J9","PicoBlade 6P","1X06","Connector_PinHeader_2.54mm:PinHeader_1x06_P2.54mm_Vertical","1"
"","J10","PicoBlade 6P","53261-0671","Conexiones y Pines:PicoBlade 6P","1"
"","J15,J16,J17,J18","Screw_Terminal_01x06","TB0010-500-06GR","Conexiones y Pines:Screw Terminal 6P","4"
"","TP1,TP2,TP3,TP4,TP5,TP6,TP7,TP8","TestPoint","5271","TestPoint:TestPoint_Loop_D2.60mm_Drill1.6mm_Beaded","8"
"","IC3,IC4,IC6,IC8,IC9","TPS62136RGXR","TPS62136RGXR","ICs - Gestión de Energía:TPS621361RGXT","5"
"","IC1,IC2","TPS621361","TPS621361RGXR","ICs - Gestión de Energía:TPS621361RGXT","2"
"","J19","~","TB0010-500-02GR","Conexiones y Pines:Screw Terminal 2P","1"

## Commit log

2025-11-10 01 - Simulaciones PSpice for TI 2024
